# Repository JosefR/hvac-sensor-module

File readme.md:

# Villa Control - HVAC Sensor Module

A simple sonsor module for measuring room temperature and humidity with a CAN
bus interface.

Power: 5-36 V DC

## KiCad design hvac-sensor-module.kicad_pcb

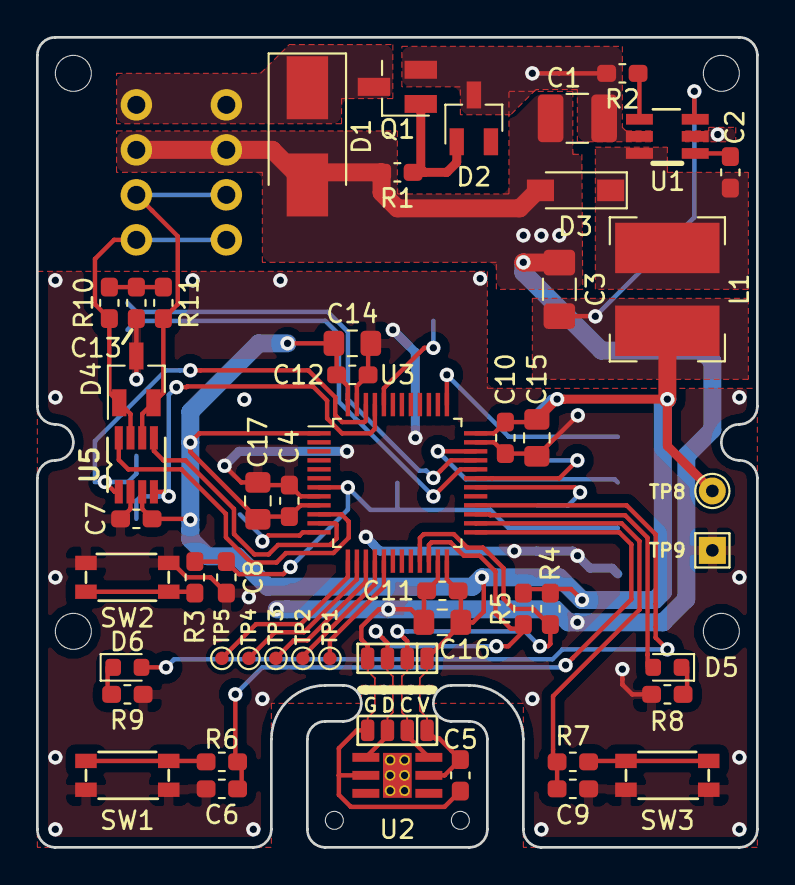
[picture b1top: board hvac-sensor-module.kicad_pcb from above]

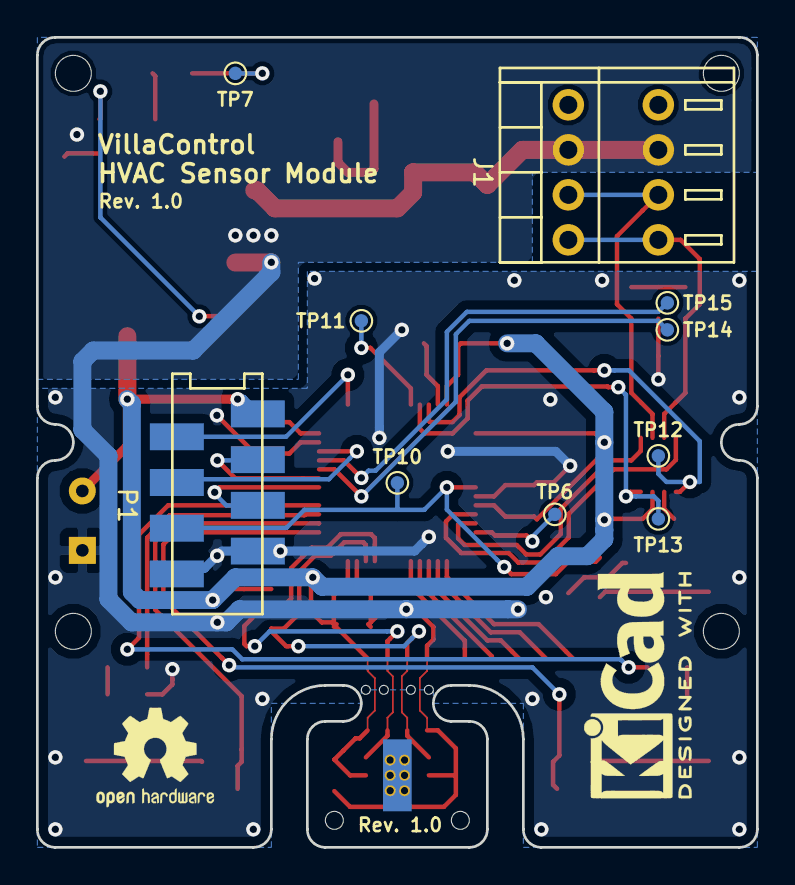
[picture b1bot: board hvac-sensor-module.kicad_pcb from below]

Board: 2 copper layers, 40.0 x 45.0 mm, 62 parts (10 on the bottom side), 40 nets.

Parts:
C1: 2.2µF; C_1210_3225Metric_Pad1.42x2.65mm_HandSolder
C2, C4, C5, C6, C7, C8, C9, C10, C11, C12: 100n; C_0603_1608Metric_Pad1.05x0.95mm_HandSolder
C3: 22µF; C_1206_3216Metric_Pad1.42x1.75mm_HandSolder
C13: 4n7; C_0603_1608Metric_Pad1.05x0.95mm_HandSolder
C14, C15, C16, C17: 4µ7; C_0805_2012Metric_Pad1.15x1.40mm_HandSolder
D1: 40.2V; D_SMB_Handsoldering
D2: 10V; D_SOT-23_ANK_Handsolder
D3: 50V Vrrm 1A; D_SOD-123_Handsolder
D4: NUP2105L; SOT-23_Handsoldering
D5, D6: red; LED_0603_1608Metric_Pad0.88x0.95mm_HandSolder
J1: Conn_01x04; WAGO_218-104
J2, J3: Sensor; Solder_Connecor_1x04
L1: 27µH 220mΩ; L_Bourns-SDR0604
P1: Debug; micromatch_smd_2x04
Q1: FDN5618P; SuperSOT-3_HandSoldering
R1, R2: 100k; R_0603_1608Metric_Pad1.05x0.95mm_HandSolder
R3, R8, R9: 220; R_0603_1608Metric_Pad1.05x0.95mm_HandSolder
R4, R5, R6, R7: 3.3k; R_0603_1608Metric_Pad1.05x0.95mm_HandSolder
R10, R11: 60.4 1%; R_0603_1608Metric_Pad1.05x0.95mm_HandSolder
SW1, SW2, SW3: SW_PUSH; KMR2_HandSolder
TP1: PA7; TestPoint_Pad_D0.75mm
TP2: PA6; TestPoint_Pad_D0.75mm
TP3: PA5; TestPoint_Pad_D0.75mm
TP4: PA4; TestPoint_Pad_D0.75mm
TP5: USART2_RX; TestPoint_Pad_D0.75mm
TP6: USART2_TX; TestPoint_Pad_D0.75mm
TP7: VINC; TestPoint_Pad_D0.75mm
TP8: 3.3V; TestPoint_THTPad_D1.5mm_Drill0.7mm
TP9: GND; TestPoint_THTPad_1.5x1.5mm_Drill0.7mm
TP10: NRST; TestPoint_Pad_D0.75mm
TP11: BOOT0; TestPoint_Pad_D0.75mm
TP12: CAN_TX; TestPoint_Pad_D0.75mm
TP13: CAN_RX; TestPoint_Pad_D0.75mm
TP14: USB_D-; TestPoint_Pad_D0.75mm
TP15: USB_D+; TestPoint_Pad_D0.75mm
U1: LMR16006; TI-DDC_HandSoldering
U2: HDC1080; HDC1080_HandSoldering
U3: STM32F072C8Tx; LQFP-48_7x7mm_P0.5mm
U5: TCAN334; TI-DCN

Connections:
+3.3VADC: C3.1, C4.1, C5.1, C7.1, C10.1, C11.1, C12.1, C14.1, C15.1, C16.1, C17.1, J2.1, J3.1, L1.2, P1.1, R4.1, R5.1, TP8.1, U1.3, U2.5, U3.1, U3.9, U3.24, U3.36, U3.48, U5.3
+VIN: D1.1, J1.1, Q1.3
/microcontroller/NRST: C8.1, P1.6, R3.1, TP10.1, U3.7
/microcontroller/SCL: J2.2, J3.2, R4.2, U2.6, U3.21
/microcontroller/SDA: J2.3, J3.3, R5.2, U2.1, U3.22
/microcontroller/SWCLK: P1.2, U3.37
/microcontroller/SWDIO: P1.4, U3.34
/microcontroller/UART1_RX: P1.3, U3.31
/microcontroller/UART1_TX: P1.5, U3.30
/power supply/VIN_DCDC: C1.1, D2.1, Q1.2, R2.2, TP7.1, U1.5
CANH_IN: D4.1, J1.4, R10.1, U5.7
CANL_IN: D4.2, J1.3, R11.2, U5.6
GND: C1.2, C3.2, C4.2, C5.2, C6.2, C7.2, C8.2, C9.2, C10.2, C11.2, C12.2, C13.2, C14.2, C15.2, C16.2, C17.2, D1.2, D3.2, D4.3, J1.2, J2.4, J3.4, P1.7, P1.8, R1.2, R8.1, R9.1, SW1.1, SW2.1, SW3.1, TP9.1, U1.2, U2.2, U3.8, U3.23, U3.35, U3.47, U5.2
unnamed: C2.1, D3.1, L1.1, U1.6
unnamed: C2.2, U1.1
unnamed: C6.1, R6.1, U3.25
unnamed: C9.1, R7.1, U3.26
unnamed: C13.1, R10.2, R11.1
unnamed: D2.2, Q1.1, R1.1
unnamed: D5.1, R8.2
unnamed: D5.2, U3.27
unnamed: D6.1, R9.2
unnamed: D6.2, U3.28
unnamed: R2.1, U1.4
unnamed: R3.2, SW2.2
unnamed: R6.2, SW1.2
unnamed: R7.2, SW3.2
unnamed: TP1.1, U3.17
unnamed: TP2.1, U3.16
unnamed: TP3.1, U3.15
unnamed: TP4.1, U3.14
unnamed: TP5.1, U3.13
unnamed: TP6.1, U3.12
unnamed: TP11.1, U3.44
unnamed: TP12.1, U3.46, U5.1
unnamed: TP13.1, U3.45, U5.4
unnamed: TP14.1, U3.32
unnamed: TP15.1, U3.33
unnamed: U3.10, U5.8
unnamed: U3.11, U5.5

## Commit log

2018-12-27 HVAC Sensor Module Project
2018-12-28 Save before merge.
2018-12-28 Pepare footprint assignment (and clean up library issues).
2019-01-02 Layout finished.
2019-01-02 Create PCB panel.
2019-01-03 Update D1.
2019-01-03 Change test point.
2019-01-03 Clean up references.
2019-01-04 Update some footprints and fine tuning.
2019-01-05 some cleanup
2019-01-05 Add BOM and renderings.
2019-01-08 Plot single PCB
2019-01-09 Add some logos to PCB and update panel.
2019-06-24 Update Rendering, Schmatic plot.
2019-06-24 Add image of board to readme
